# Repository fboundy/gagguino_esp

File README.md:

Gagguino ESP – ESP32 Firmware for Gaggia Classic
================================================

An ESP32-based controller for the Gaggia Classic espresso machine featuring PID temperature control (MAX31865 + PT100), flow/pressure/shot timing, MQTT with Home Assistant discovery, and robust OTA updates.

Features
--------
- PID temperature control using MAX31865 (PT100) with anti-windup and derivative on measurement.
- Heater control via time-proportioning PWM windowing.
- Flow pulses → volume, pressure sampling with moving average, and shot timing.
- Wi‑Fi + MQTT (PubSubClient) with Home Assistant discovery (sensors, numbers, switch, binary sensors).
- ArduinoOTA with safety handling (heater disabled during OTA).

Hardware / Pinout (ESP32 dev board defaults)
-------------------------------------------
- `FLOW_PIN` 26: Flow sensor input (interrupt on CHANGE)
- `ZC_PIN` 25: AC zero‑cross detect (interrupt on RISING)
- `HEAT_PIN` 27: Boiler relay/SSR output (time‑proportioning)
- `AC_SENS` 14: Steam switch sense (digital input)
- `MAX_CS` 16: MAX31865 SPI chip‑select
- `PRESS_PIN` 35: Analog pressure sensor input

Getting Started
---------------
1) Prerequisites
- PlatformIO (VS Code extension or CLI)
- Libraries are managed by PlatformIO via `platformio.ini` (`Adafruit MAX31865`, `PubSubClient`).

2) Configure secrets
- Edit `src/secrets.h` and set:
  - `WIFI_SSID`, `WIFI_PASSWORD`
  - `MQTT_HOST`, `MQTT_PORT`, `MQTT_CLIENTID`, `MQTT_USER`, `MQTT_PASS`
- Tip: Avoid committing real credentials. Consider ignoring or templating this file in your fork.

3) Build and upload (USB)
- Set board/environment in `platformio.ini` (default `esp32dev`).
- Build: `pio run`
- Upload (USB): `pio run -t upload`
- Monitor: `pio device monitor -b 115200`

4) OTA uploads (Wi‑Fi)
- `platformio.ini` includes an `esp32dev_ota` env with `upload_protocol = espota`.
- Set your device IP in `upload_port` (e.g. `192.168.4.99`).
- Upload over Wi‑Fi: `pio run -e esp32dev_ota -t upload`
- Optional OTA password:
  - In `platformio.ini` add build flag: `-D OTA_PASSWORD="your-password"` (or `OTA_PASSWORD_HASH`)
  - Match the `--auth` flag under `upload_flags` for `espota`.
- Enable OTA via MQTT before uploading (opens a ~5 min window and pauses normal MQTT):
  - `mosquitto_pub -h <broker> -t gaggia_classic/<UID>/ota/enable -n`
  - Device resumes normal servicing when the update completes or the window expires.

Home Assistant Integration
--------------------------
- Discovery prefix: `homeassistant` (configurable in code).
- Device base: `gaggia_classic` with a unique MAC‑derived suffix per device.
- Entities (auto‑created on first connect):
  - Sensors: Shot Volume (mL), Set Temperature (°C), Current Temperature (°C), Pressure (bar), Shot Time (s), OTA Status
  - Binary sensors: Shot, Pre‑Flow, Steam
  - Numbers (settable): Brew Setpoint (90–99 °C), Steam Setpoint (145–155 °C), PID P/I/D/Guard
  - Switch: Heater Enable

MQTT Topics
-----------
- Base topics: `gaggia_classic/<UID>/...` where `<UID>` is derived from MAC (stable per device).
- Commands vs state follow the pattern: `/set` for commands, `/state` for retained/current values.

Examples (replace `<UID>` accordingly):
```
# Set brew temperature to 95 °C
mosquitto_pub -h <broker> -t gaggia_classic/<UID>/brew_setpoint/set -m 95

# Adjust PID gains
mosquitto_pub -h <broker> -t gaggia_classic/<UID>/pid_p/set -m 20.0
mosquitto_pub -h <broker> -t gaggia_classic/<UID>/pid_i/set -m 1.0
mosquitto_pub -h <broker> -t gaggia_classic/<UID>/pid_d/set -m 100.0
mosquitto_pub -h <broker> -t gaggia_classic/<UID>/pid_guard/set -m 20.0

# Heater ON/OFF
mosquitto_pub -h <broker> -t gaggia_classic/<UID>/heater/set -m ON
mosquitto_pub -h <broker> -t gaggia_classic/<UID>/heater/set -m OFF

# Enable OTA window (~5 min)
mosquitto_pub -h <broker> -t gaggia_classic/<UID>/ota/enable -n
```

Tuning & Behavior
-----------------
- Brew setpoint limits: 90–99 °C. Steam setpoint limits: 145–155 °C (default 152 °C).
- PID defaults (overridable via MQTT numbers): `P=20.0`, `I=1.0`, `D=100.0`, `Guard=20.0`.
- Pressure: analog read with linear conversion; intercept is auto‑zeroed at boot if near 0 bar.
- Heater: time‑proportioning window (`PWM_CYCLE`) with dynamic ON time from PID result.

Troubleshooting
---------------
- Serial monitor at `115200` shows boot logs, Wi‑Fi/MQTT status, and optional periodic diagnostics.
- MAX31865 diagnostics: firmware logs faults and raw/temperature reads to help validate wiring.
- OTA: Device hostname is derived from MAC (e.g. `gaggia-ABCDEF`). During OTA the heater is forced off and other work is throttled.

Safety
------
- Mains voltage is dangerous. Ensure proper isolation, fusing, and enclosure.
- Verify all pin mappings, voltages, and grounds before powering the machine.

Project Layout
--------------
- `src/gagguino.cpp` – main firmware logic, OTA/MQTT/HA, PID, sensors.
- `src/gagguino.h` – public entry points for `setup()`/`loop()` in the `gag` namespace.
- `src/main.cpp` – minimal sketch bridging Arduino to `gag::setup/loop`.
- `src/secrets.h` – Wi‑Fi and MQTT configuration.
- `platformio.ini` – environments, dependencies, and OTA settings.

License
-------
See `LICENSE`.

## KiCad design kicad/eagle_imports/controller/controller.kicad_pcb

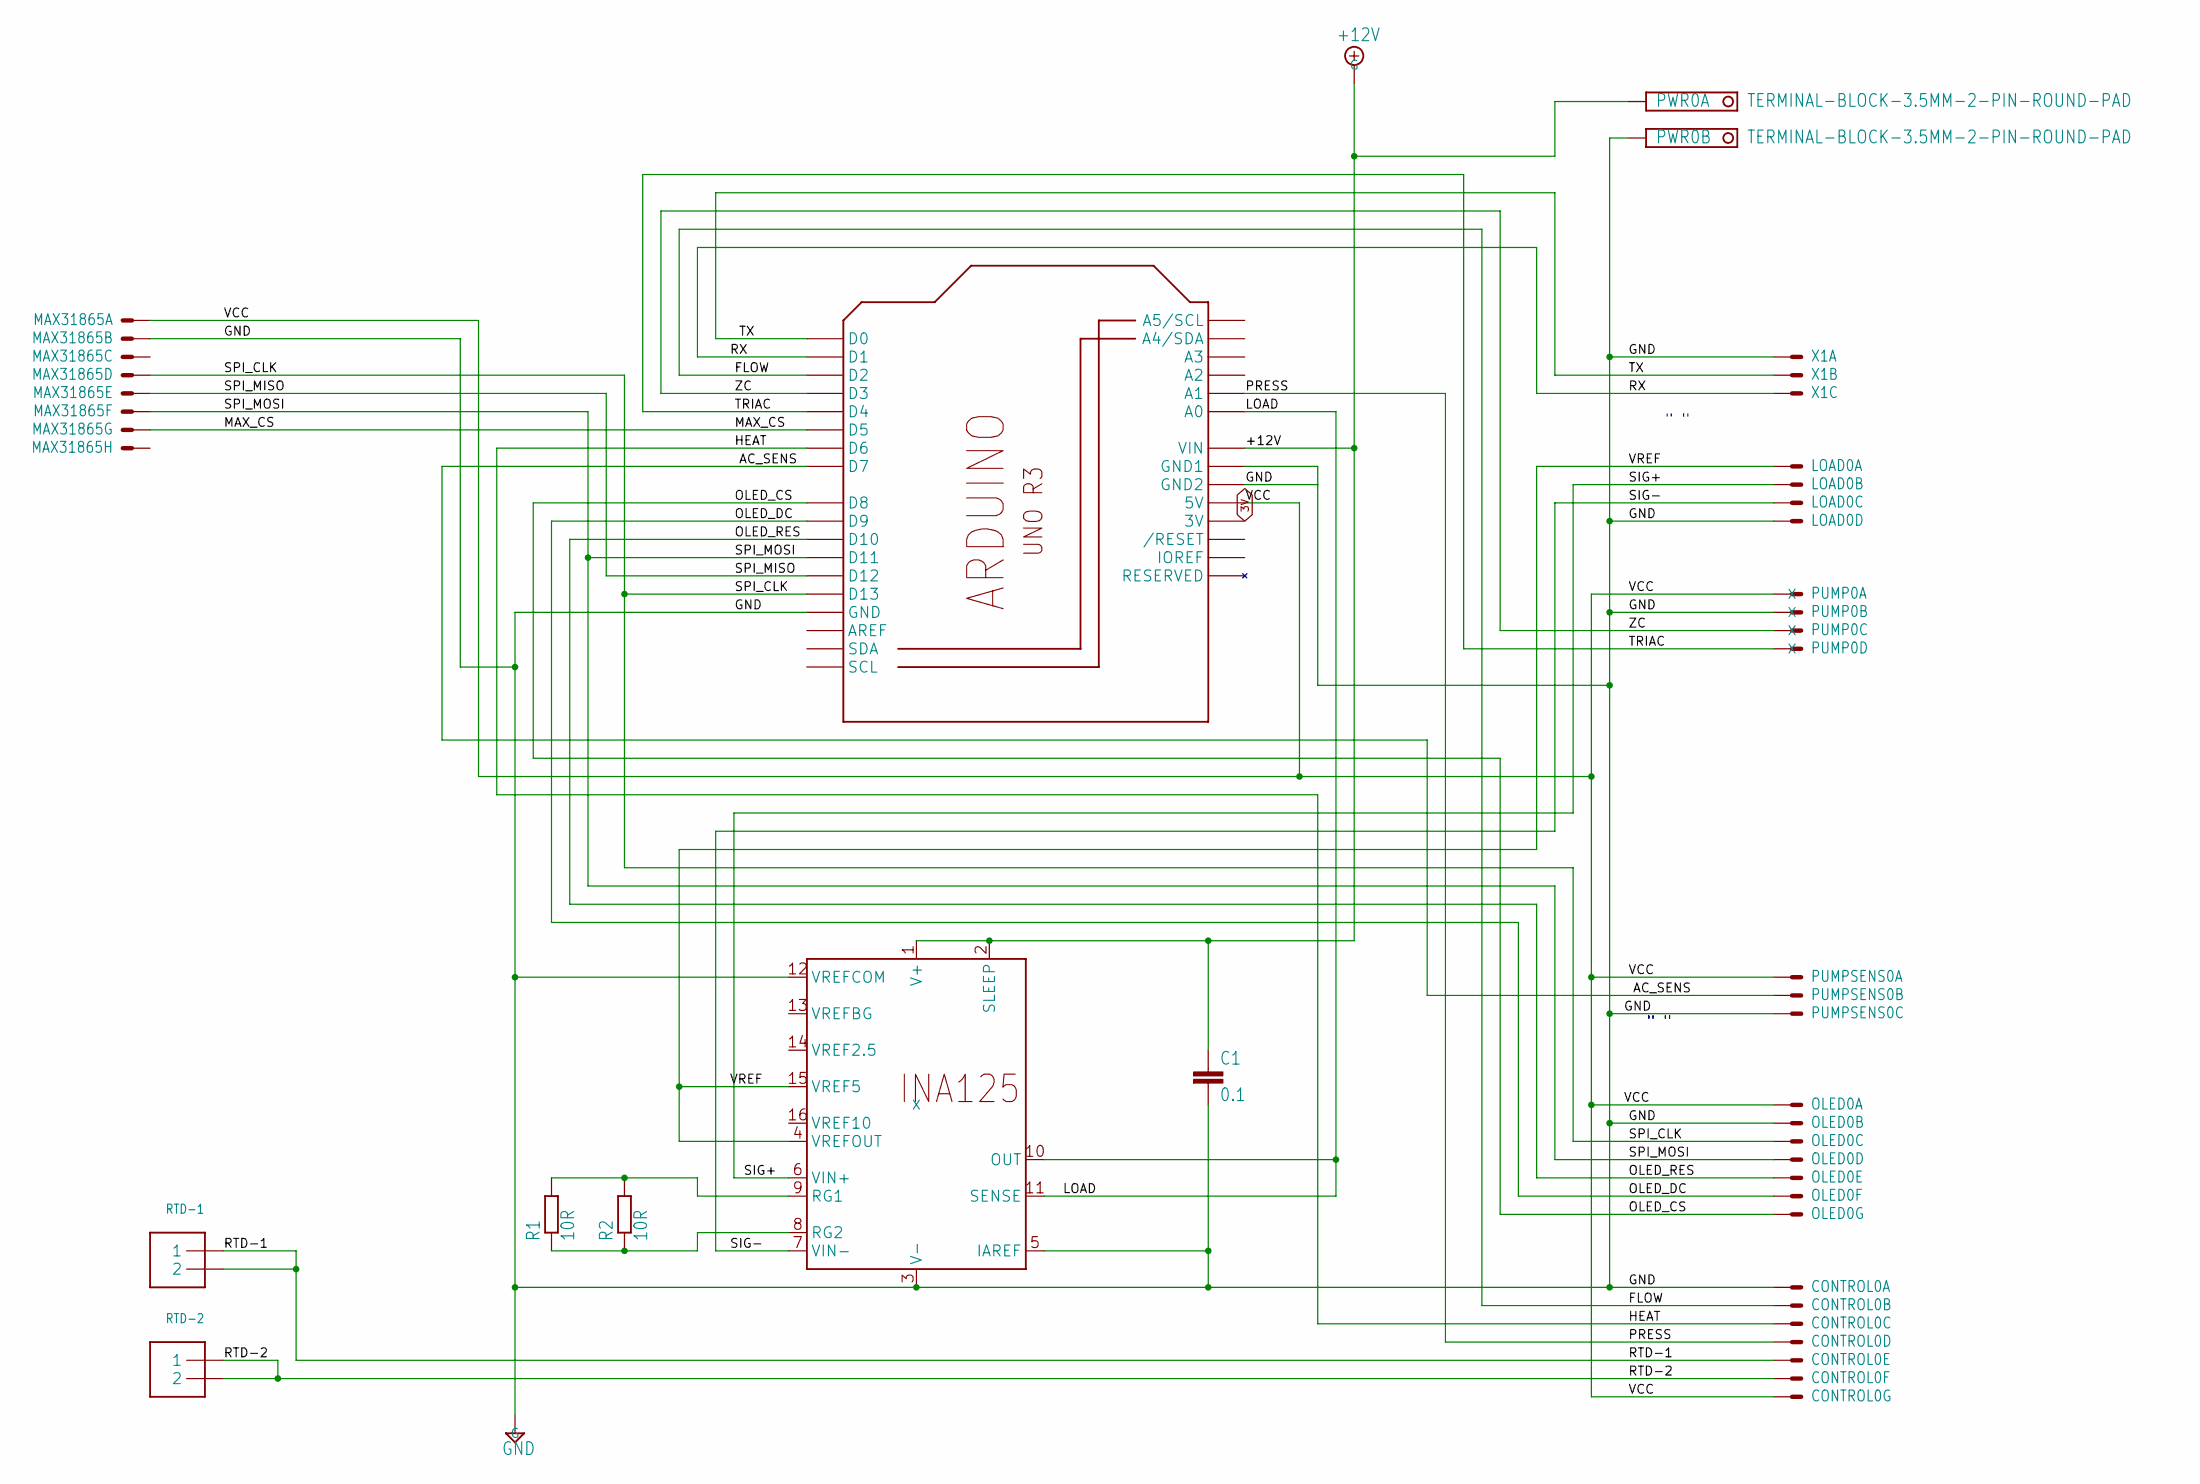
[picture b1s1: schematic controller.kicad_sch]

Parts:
C1: 0.1; C025-025X050
CONTROL0: 22-23-2071
IC1: INA125; DIL16
LOAD0: 22-23-2041
MAX31865: 22-23-2081
OLED0: 22-23-2071
PUMP0: 22-23-2041
PUMPSENS0: 22-23-2031
PWR0: TERMINAL-BLOCK-3.5MM-2-PIN-ROUND-PAD; TERMINAL-BLOCK-2-PIN-3.5MM-ROUND-PAD
R1, R2: 10R; 0309_12
RTD-1, RTD-2: TERMBLOCK_1X2; TERMBLOCK_1X2-3.5MM
U1: ARDUINOR3-BPLACE
X1: 22-23-2031

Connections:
3V: U1.3V
+12V: C1.1, IC1.1 (V+), IC1.2 (SLEEP), PWR0.1, U1.VIN
AC_SENS: PUMPSENS0.2, U1.D7
FLOW: CONTROL0.2, U1.D2
GND: C1.2, CONTROL0.1, IC1.3 (V-), IC1.5 (IAREF), IC1.12 (VREFCOM), LOAD0.4, MAX31865.2, OLED0.2, PUMP0.2, PUMPSENS0.3, PWR0.2, U1.GND, U1.GND1, U1.GND2, X1.1
HEAT: CONTROL0.3, U1.D6
LOAD: IC1.10 (OUT), IC1.11 (SENSE), U1.A0
MAX_CS: MAX31865.7, U1.D5
OLED_CS: OLED0.7, U1.D8
OLED_DC: OLED0.6, U1.D9
OLED_RES: OLED0.5, U1.D10
PRESS: CONTROL0.4, U1.A1
RG1: IC1.9 (RG1), R1.2, R2.2
RG2: IC1.8 (RG2), R1.1, R2.1
RTD-1: CONTROL0.5, RTD-1.1, RTD-1.2
RTD-2: CONTROL0.6, RTD-2.1, RTD-2.2
RX: U1.D1, X1.3
SIG+: IC1.6 (VIN+), LOAD0.2
SIG-: IC1.7 (VIN-), LOAD0.3
SPI_CLK: MAX31865.4, OLED0.3, U1.D13
SPI_MISO: MAX31865.5, U1.D12
SPI_MOSI: MAX31865.6, OLED0.4, U1.D11
TRIAC: PUMP0.4, U1.D4
TX: U1.D0, X1.2
VCC: CONTROL0.7, MAX31865.1, OLED0.1, PUMP0.1, PUMPSENS0.1, U1.5V
VREF: IC1.4 (VREFOUT), IC1.15 (VREF5), LOAD0.1
ZC: PUMP0.3, U1.D3

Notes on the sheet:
" "

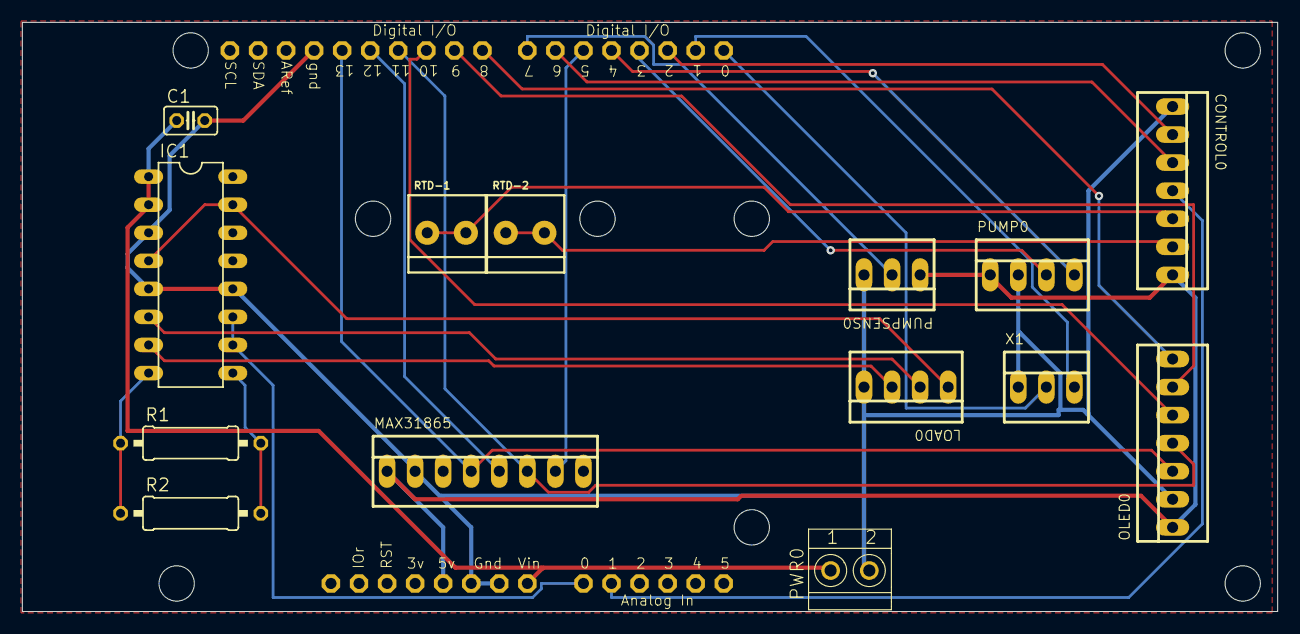
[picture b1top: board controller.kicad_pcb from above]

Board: 4 copper layers, 113.6 x 53.3 mm, 23 parts (0 on the bottom side), 26 nets.

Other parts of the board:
UNK_HOLE_0: dummyfp0
UNK_HOLE_1: dummyfp1
UNK_HOLE_2: dummyfp2
UNK_HOLE_3: dummyfp3
UNK_HOLE_4: dummyfp4
UNK_HOLE_5: dummyfp5
UNK_HOLE_6: dummyfp6
UNK_HOLE_7: dummyfp7

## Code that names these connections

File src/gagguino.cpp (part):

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 * - Robust OTA (ArduinoOTA) that throttles other work while an update runs.
 *
 * Hardware pins (ESP32 default board mapping):
 * - FLOW_PIN (26)   : Flow sensor input (interrupt on CHANGE)
 * - ZC_PIN (25)     : AC zero‑cross detect (interrupt on RISING)
 * - HEAT_PIN (27)   : Boiler relay/SSR output (PWM windowing)
 * - AC_SENS (14)    : Steam switch sense (digital input)
 * - MAX_CS (16)     : MAX31865 SPI chip‑select
 * - PRESS_PIN (35)  : Analog pressure sensor input
 */
#include "gagguino.h"

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 */

namespace {
constexpr int FLOW_PIN = 26, ZC_PIN = 25, HEAT_PIN = 27, AC_SENS = 14;
constexpr int MAX_CS = 16;
constexpr int PRESS_PIN = 35;

constexpr unsigned long PRESS_CYCLE = 100, PID_CYCLE = 250, PWM_CYCLE = 250,
                   ESP_CYCLE = 500, LOG_CYCLE = 2000;
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        otaStart = millis();
        publishStr(t_ota_state, "active", true);
        // Turn off heater to reduce power/noise during OTA
        digitalWrite(HEAT_PIN, LOW);
        heaterState = false;
    });
    ArduinoOTA.onEnd([]() {
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        otaStart = 0;
        publishStr(t_ota_state, "idle", true);
        // (Optional) re-attach interrupts if you detached them on start
        // attachInterrupt(digitalPinToInterrupt(FLOW_PIN), flowInt, CHANGE);
        // attachInterrupt(digitalPinToInterrupt(ZC_PIN), zcInt, RISING);
    });
    ArduinoOTA.setTimeout(120000);  // 120s OTA socket timeout (default is shorter)
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 */
static void updateTempPWM() {
    if (!heaterEnabled) {
        digitalWrite(HEAT_PIN, LOW);
        heaterState = false;
        return;
    }
    if (currentTime - lastPwmTime >= (unsigned long)heatCycles) {
        digitalWrite(HEAT_PIN, HIGH);
        heaterState = true;
    }
    if (currentTime - lastPwmTime >= PWM_CYCLE) {
        digitalWrite(HEAT_PIN, LOW);
        heaterState = false;
        lastPwmTime = currentTime;
        nLoop = 0;
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 * @brief Sample pressure ADC and maintain a moving average buffer.
 */
static void updatePressure() {
    rawPress = analogRead(PRESS_PIN);
    pressNow = rawPress * pressGrad + pressInt;
    uint8_t idx = pressBuffIdx;
    pressSum -= pressBuff[idx];
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    heaterEnabled = false;
    heatPower = 0.0f;
    heatCycles = PWM_CYCLE;
    digitalWrite(HEAT_PIN, LOW);
    heaterState = false;
}

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    analogSetAttenuation(ADC_11db);
#endif

    pinMode(MAX_CS, OUTPUT);
    pinMode(HEAT_PIN, OUTPUT);
    pinMode(PRESS_PIN, INPUT);
    pinMode(FLOW_PIN, INPUT_PULLUP);
    pinMode(ZC_PIN, INPUT);
    pinMode(AC_SENS, INPUT_PULLUP);
    digitalWrite(HEAT_PIN, LOW);
    heaterState = false;

    // Initialize MAX31865 (set wiring: 2/3/4-wire as appropriate)
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    lastTemp = currentTemp;

    // zero pressure
    float startP = analogRead(PRESS_PIN) * pressGrad + pressInt;
    if (startP > -PRESS_TOL && startP < PRESS_TOL) {
        pressInt -= startP;
        LOG("Pressure Intercept reset to %f", pressInt);
    }

    attachInterrupt(digitalPinToInterrupt(FLOW_PIN), flowInt, RISING);
    attachInterrupt(digitalPinToInterrupt(ZC_PIN), zcInt, RISING);

    pulseCount = 0;
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    initMqttTuning();
    resolveBrokerIfNeeded();

    LOG("Pins: FLOW=%d ZC=%d HEAT=%d AC_SENS=%d PRESS=%d  SPI{CS=%d}", FLOW_PIN, ZC_PIN, HEAT_PIN,
        AC_SENS, PRESS_PIN, MAX_CS);
    LOG("WiFi: connecting to '%s'…  MQTT: %s:%u id=%s", WIFI_SSID, MQTT_HOST, MQTT_PORT,
        MQTT_CLIENTID);
}
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        // (Optional) Detach high-rate ISRs during OTA to reduce CPU/latency spikes
        // static bool isrDetached = false;
        // if (!isrDetached) {
        //     detachInterrupt(digitalPinToInterrupt(FLOW_PIN));
        //     detachInterrupt(digitalPinToInterrupt(ZC_PIN));
        //     isrDetached = true;
        // }
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
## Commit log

2025-09-04 Testing
2025-09-05 More logging. Debugging hardware
2025-09-05 Codex review changes
2025-09-05 OTA Loggiing
2025-09-05 MQTT: publish ac/zc/pulse counters; HA: add PID number entities (P/I/D/Guard) with MQTT control; publish PID states; clamp PID with i==0 safe; discovery for new sensors
2025-09-05 Fix: forward-declare publishStr for use in ArduinoOTA callbacks
2025-09-05 Build: remove duplicate default arg on publishStr definition (forward decl keeps default)
2025-09-05 PIO Environment
2025-09-05 PIO env
2025-09-05 vscode setting
2025-09-05 OTA Upload Config
2025-09-05 Heater On/Off Switch
2025-09-05 Triac Prototype
2025-09-05 Docs
2025-09-08 Adjust MQTT publish interval based on shot state
2025-09-08 Refine PID controller with filtered derivative
2025-09-08 Updates CalcPID
2025-09-08 Tune default PID gains and clean derivative state
2025-09-08 Refine MQTT publish timing
2025-09-08 Use shorter MQTT publish intervals
2025-09-08 Fix MQTT names
2025-09-08 PID Updates
2025-09-08 Remove redundant setpoint topics and MAX31865 debug helpers
2025-09-08 Remove holdoff, power cap, and TRIAC control
2025-09-08 Disable heater on WiFi or MQTT drop
2025-09-08 Add MQTT error logging with rolling buffer
2025-09-08 Reinstate Max31865 begin method
2025-09-08 WiFi Stability
2025-09-08 Use ISR-safe timer for flow and zero-cross interrupts
2025-09-08 feat: add non-blocking wifi reconnect
2025-09-08 Cast waitForConnectResult to wl_status_t
2025-09-08 Add MQTT OTA enable command with auto timeout
2025-09-08 Publish only on value change
2025-09-08 Retain MQTT publications
2025-09-09 Publish ESP-NOW diagnostics via MQTT
2025-09-09 Add ESP-NOW packet structure
2025-09-09 Add ESP-NOW packet transmission
